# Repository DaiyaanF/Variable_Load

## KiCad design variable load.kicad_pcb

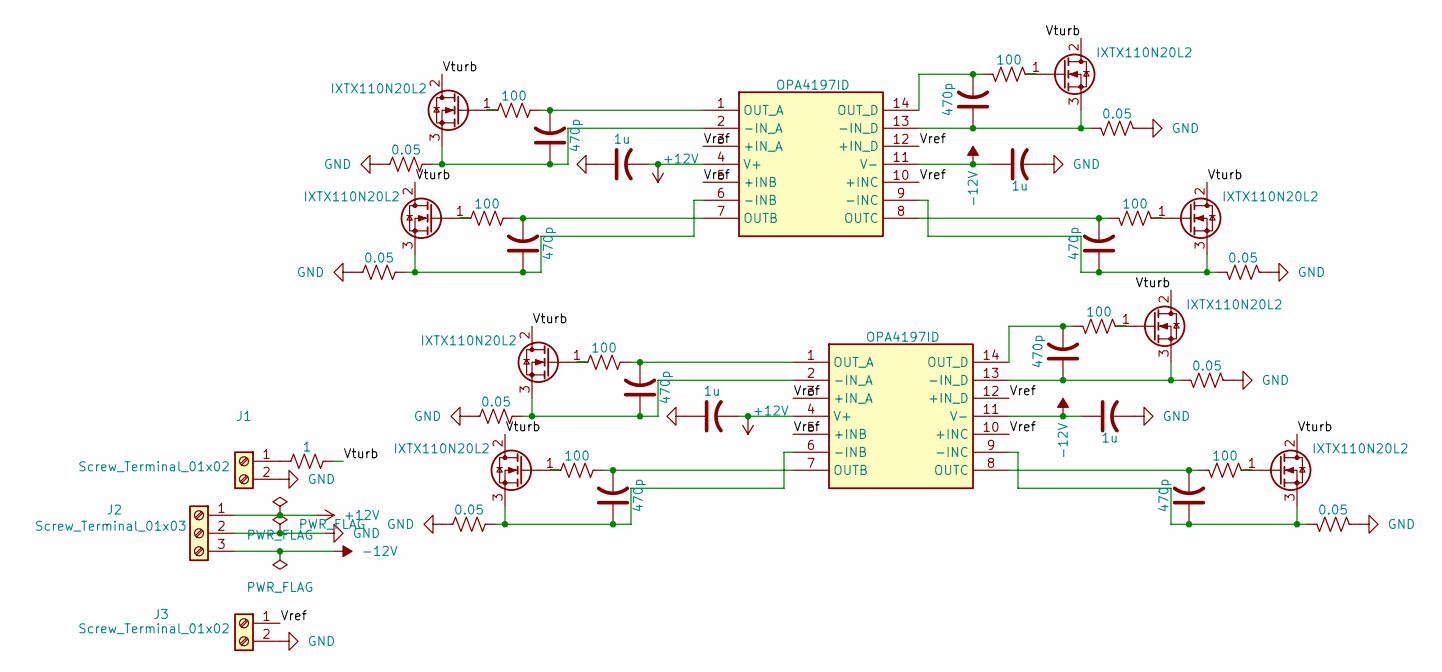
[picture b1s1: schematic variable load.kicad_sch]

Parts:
C1, C2, C9, C11: 1u; C_0805_2012Metric
C3, C4, C5, C6, C7, C8, C10, C12: 470p; C_0805_2012Metric
IC1, IC2: OPA4197ID; SOIC-14_3.9x8.7mm_P1.27mm; Manufacturer_Part_Number OPA4172IDR; Mouser Part Number 595-OPA4172IDR
J1, J3: Screw_Terminal_01x02; TerminalBlock_Phoenix_MKDS-1,5-2_1x02_P5.00mm_Horizontal
J2: Screw_Terminal_01x03; TerminalBlock_Phoenix_MKDS-1,5-3_1x03_P5.00mm_Horizontal
Q1, Q2, Q3, Q4, Q5, Q6, Q7, Q8: IXTX110N20L2; TO-247-3_Vertical
R1, R3, R5, R7, R9, R10, R14, R16: 0.05; R_2512_6332Metric
R2, R4, R6, R8, R11, R12, R13, R15: 100; R_0805_2012Metric
R17: 1; R_2512_6332Metric

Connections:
+12V: C1.2, C9.2, IC1.4 (V+), IC2.4 (V+), J2.1
-12V: C2.1, C11.1, IC1.11 (V-), IC2.11 (V-), J2.3
/Vref: IC1.3 (+IN_A), IC1.5 (+INB), IC1.10 (+INC), IC1.12 (+IN_D), IC2.3 (+IN_A), IC2.5 (+INB), IC2.10 (+INC), IC2.12 (+IN_D), J3.1
/Vturb: Q1.2 (D), Q2.2 (D), Q3.2 (D), Q4.2 (D), Q5.2 (D), Q6.2 (D), Q7.2 (D), Q8.2 (D), R17.1
GND: C1.1, C2.2, C9.1, C11.2, J1.2, J2.2, J3.2, R1.2, R3.2, R5.2, R7.2, R9.2, R10.2, R14.2, R16.2
unnamed: C4.1, IC1.6 (-INB), Q2.3 (S), R3.1
unnamed: C5.1, IC1.9 (-INC), Q3.3 (S), R5.1
unnamed: C3.1, IC1.2 (-IN_A), Q1.3 (S), R1.1
unnamed: C6.1, IC1.13 (-IN_D), Q4.3 (S), R7.1
unnamed: C4.2, IC1.7 (OUTB), R4.1
unnamed: C5.2, IC1.8 (OUTC), R6.1
unnamed: C3.2, IC1.1 (OUT_A), R2.1
unnamed: C6.2, IC1.14 (OUT_D), R8.1
unnamed: C7.1, IC2.6 (-INB), Q5.3 (S), R9.1
unnamed: C12.1, IC2.9 (-INC), Q8.3 (S), R16.1
unnamed: C8.1, IC2.2 (-IN_A), Q6.3 (S), R10.1
unnamed: C10.1, IC2.13 (-IN_D), Q7.3 (S), R14.1
unnamed: C7.2, IC2.7 (OUTB), R11.1
unnamed: C12.2, IC2.8 (OUTC), R15.1
unnamed: C8.2, IC2.1 (OUT_A), R12.1
unnamed: C10.2, IC2.14 (OUT_D), R13.1
unnamed: J1.1, R17.2
unnamed: Q1.1 (G), R2.2
unnamed: Q2.1 (G), R4.2
unnamed: Q3.1 (G), R6.2
unnamed: Q4.1 (G), R8.2
unnamed: Q5.1 (G), R11.2
unnamed: Q6.1 (G), R12.2
unnamed: Q7.1 (G), R13.2
unnamed: Q8.1 (G), R15.2

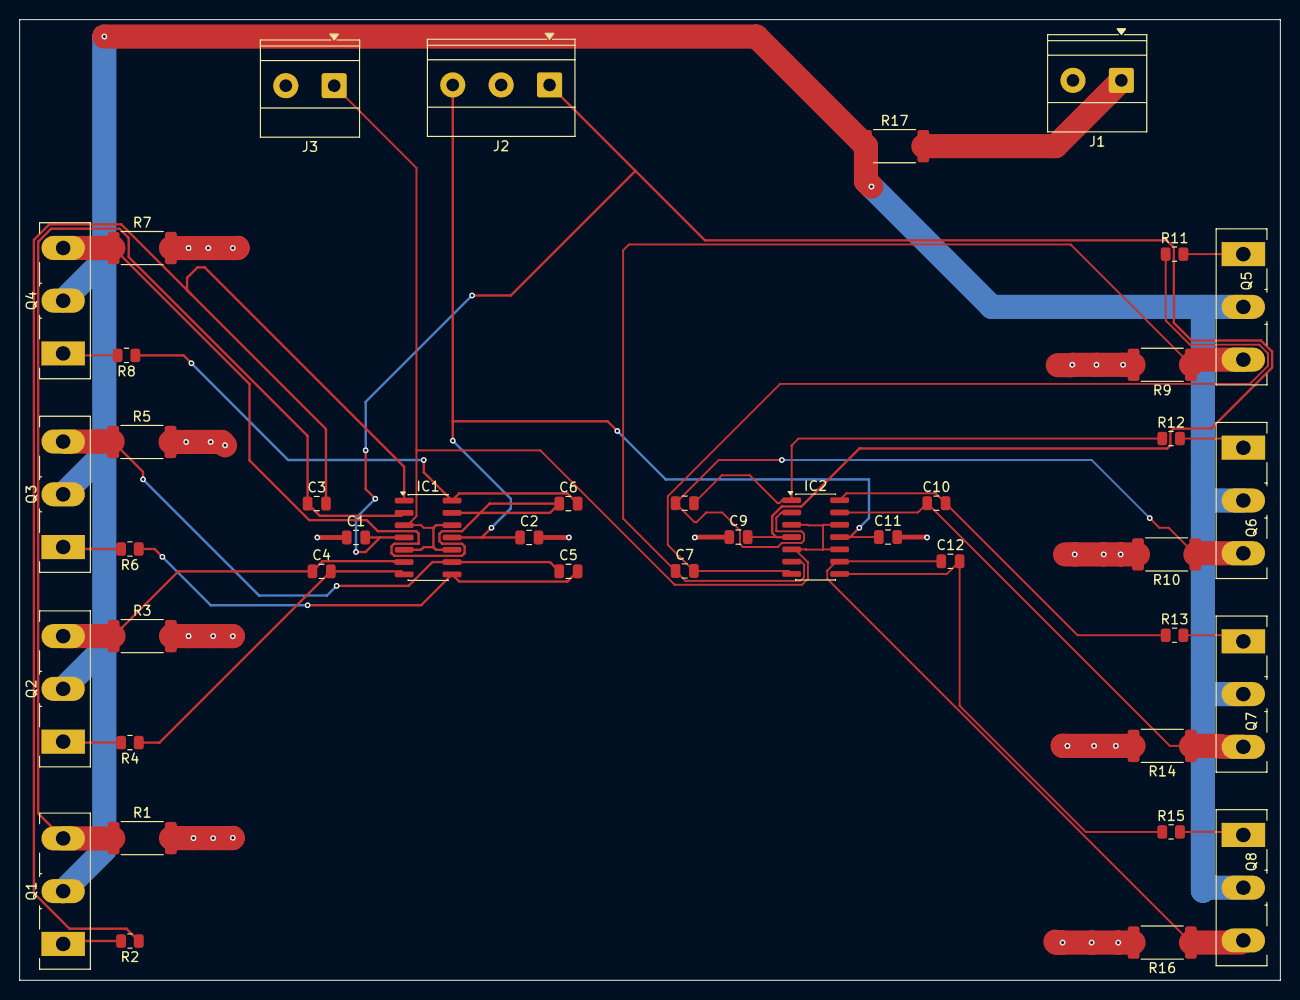
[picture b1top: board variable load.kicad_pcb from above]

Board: 2 copper layers, 130.2 x 99.2 mm, 42 parts (0 on the bottom side), 30 nets.
